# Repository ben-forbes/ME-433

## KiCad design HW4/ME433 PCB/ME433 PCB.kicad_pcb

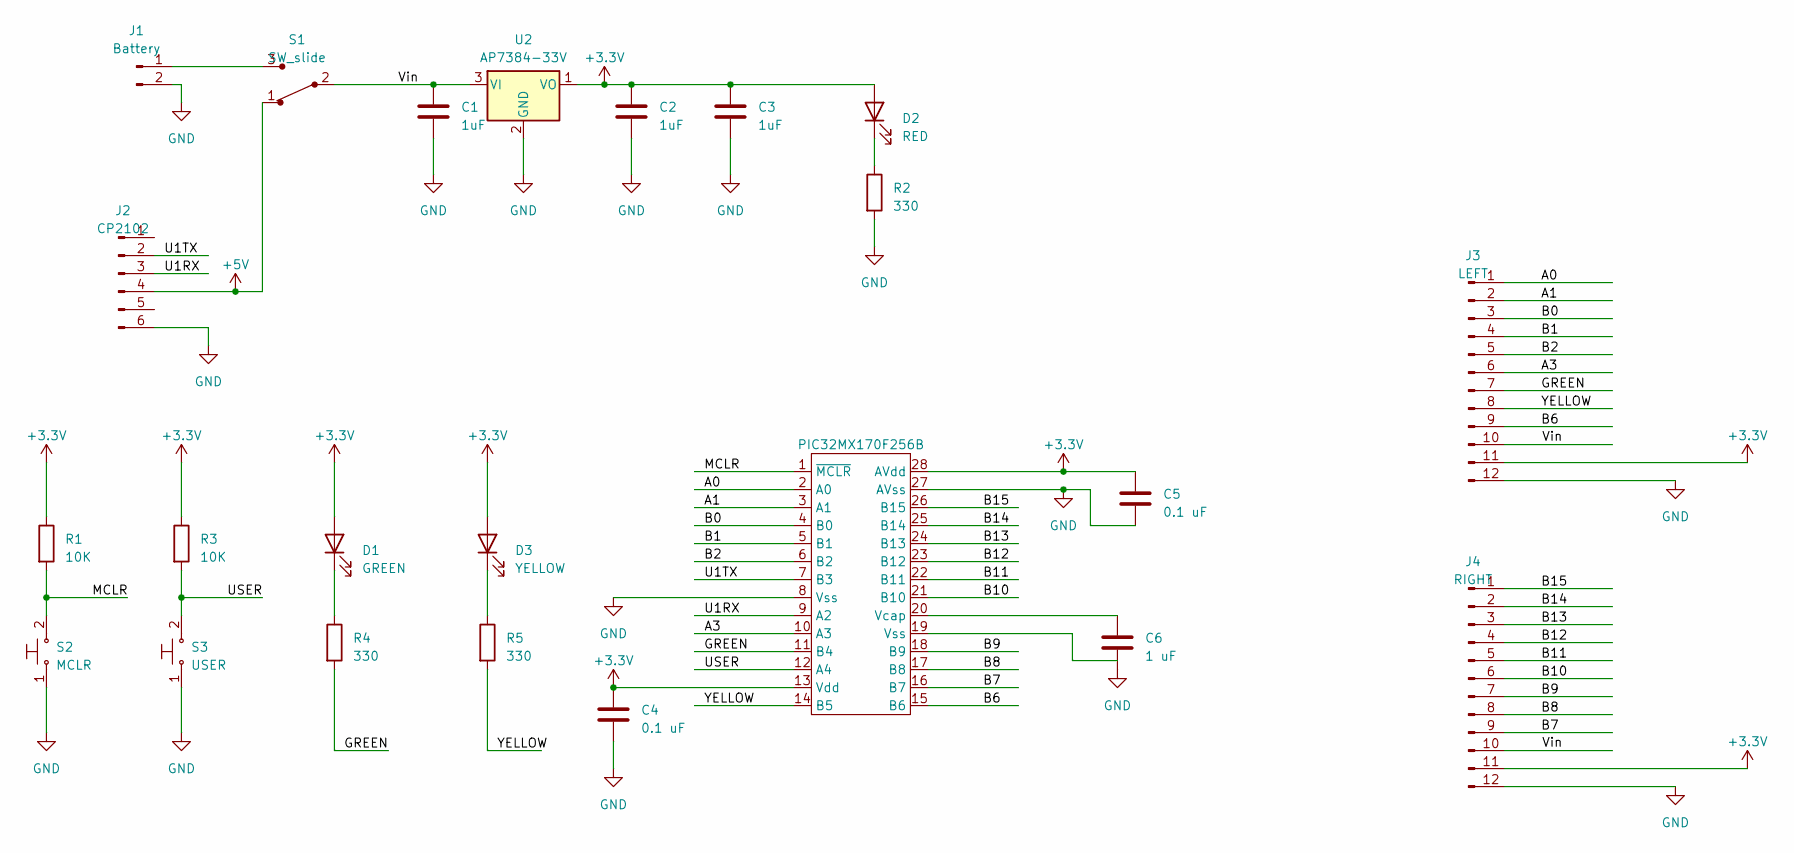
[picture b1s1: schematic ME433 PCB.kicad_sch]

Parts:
C1, C2, C3: 1uF; C_Disc_D5.1mm_W3.2mm_P5.00mm
C4, C5: 0.1 uF; C_Disc_D5.0mm_W2.5mm_P2.50mm
C6: 1 uF; C_Disc_D5.1mm_W3.2mm_P5.00mm
D1: GREEN; LED_D3.0mm
D2: RED; LED_D3.0mm
D3: YELLOW; LED_D3.0mm
J1: Battery; PinSocket_1x02_P2.54mm_Vertical
J2: CP2102; PinSocket_1x06_P2.54mm_Vertical
J3: LEFT; PinSocket_1x12_P2.54mm_Vertical
J4: RIGHT; PinSocket_1x12_P2.54mm_Vertical
R1, R3: 10K; R_Axial_DIN0207_L6.3mm_D2.5mm_P7.62mm_Horizontal
R2, R4, R5: 330; R_Axial_DIN0207_L6.3mm_D2.5mm_P7.62mm_Horizontal
S1: SW_slide; Switch_Slide_11.6x4mm_EG1218; MPN EG1218; Digi-Key_PN EG1903-ND
S2: MCLR; Push_Button; MPN GPTS203211B; Digi-Key_PN CW181-ND
S3: USER; Push_Button; MPN GPTS203211B; Digi-Key_PN CW181-ND
U1: PIC32MX170F256B; DIP-28_W7.62mm_Socket
U2: AP7384-33V; TO-92L_Inline

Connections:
+3.3V: C2.1, C3.1, C4.1, C5.1, D1.2 (A), D2.2 (A), D3.2 (A), J3.11, J4.11, R1.1, R3.1, U1.13 (Vdd), U1.28 (AVdd), U2.1 (VO)
+5V: J2.4, S1.1
/A0: J3.1, U1.2 (A0)
/A1: J3.2, U1.3 (A1)
/A3: J3.6, U1.10 (A3)
/B0: J3.3, U1.4 (B0)
/B1: J3.4, U1.5 (B1)
/B2: J3.5, U1.6 (B2)
/B6: J3.9, U1.15 (B6)
/B7: J4.9, U1.16 (B7)
/B8: J4.8, U1.17 (B8)
/B9: J4.7, U1.18 (B9)
/B10: J4.6, U1.21 (B10)
/B11: J4.5, U1.22 (B11)
/B12: J4.4, U1.23 (B12)
/B13: J4.3, U1.24 (B13)
/B14: J4.2, U1.25 (B14)
/B15: J4.1, U1.26 (B15)
/GREEN: J3.7, R4.2, U1.11 (B4)
/MCLR: R1.2, S2.2, U1.1 (~MCLR)
/U1RX: J2.3, U1.9 (A2)
/U1TX: J2.2, U1.7 (B3)
/USER: R3.2, S3.2, U1.12 (A4)
/Vin: C1.1, S1.2, U2.3 (VI)
/YELLOW: J3.8, R5.2, U1.14 (B5)
GND: C1.2, C2.2, C3.2, C4.2, C5.2, C6.2, J1.2, J2.6, J3.12, J4.12, R2.2, S2.1, S3.1, U1.8 (Vss), U1.27 (AVss), U2.2 (GND)
unnamed: D1.1 (K), R4.1
unnamed: D2.1 (K), R2.1
unnamed: D3.1 (K), R5.1
unnamed: J1.1, S1.3
unnamed: C6.1, U1.20 (Vcap)

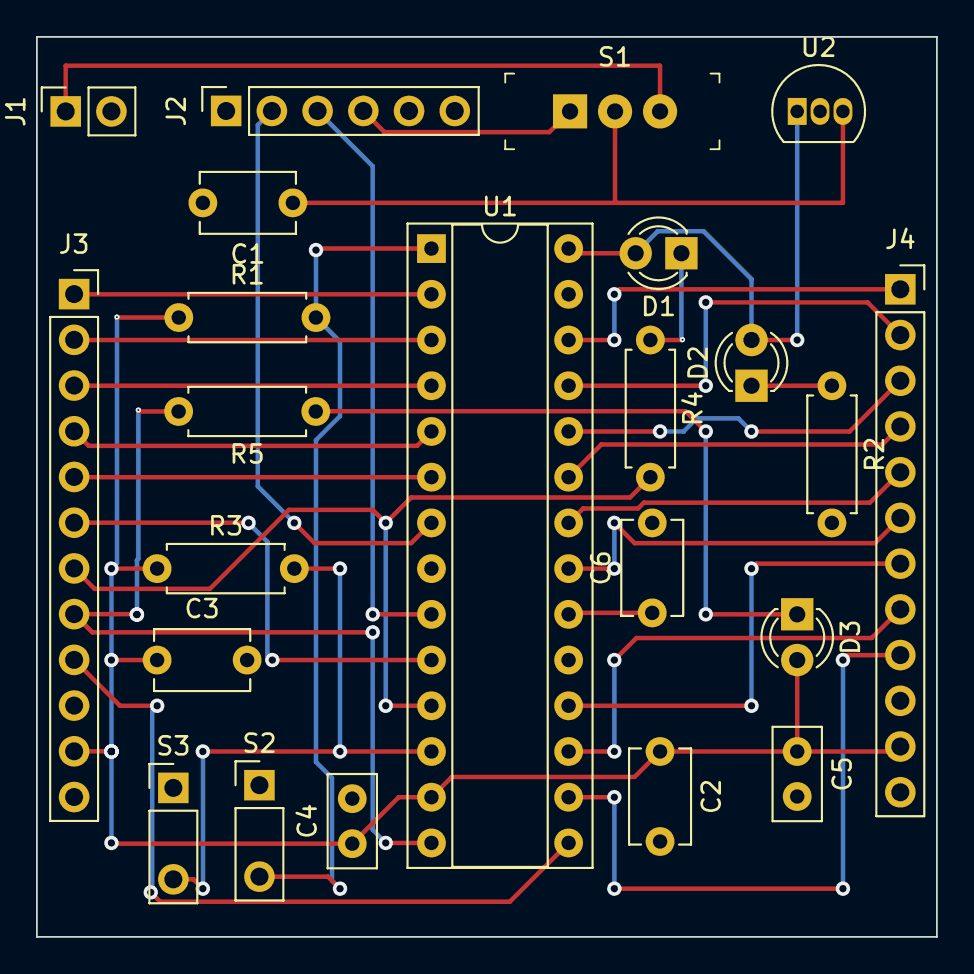
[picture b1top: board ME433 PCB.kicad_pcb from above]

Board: 2 copper layers, 50.0 x 50.0 mm, 23 parts (0 on the bottom side), 31 nets.

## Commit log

2023-04-04 Upload HW2
2023-04-05 HW3 and new HW2
2023-04-14 Start of HW 4 and 5
2023-04-27 HW8 mov
2023-05-04 HW10
    Homework 10
2023-05-04 demo
    Demo
2023-05-11 HW11
2023-05-18 HW12
2023-05-20 HW13
2023-05-24 HW14
2023-05-31 HW15
2023-06-02 HW15 part 2
2023-06-08 Robot_competition
